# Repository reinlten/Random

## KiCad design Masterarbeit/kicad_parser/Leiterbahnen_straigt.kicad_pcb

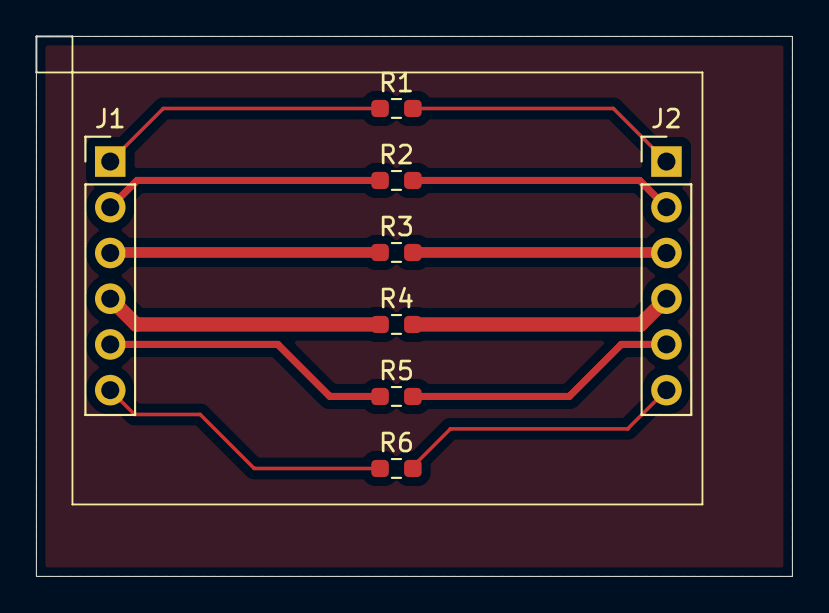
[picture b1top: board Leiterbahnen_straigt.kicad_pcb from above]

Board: 2 copper layers, 42.0 x 30.0 mm, 8 parts (0 on the bottom side), 12 nets.

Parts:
J1, J2: Conn_01x06_Pin; PinHeader_1x06_P2.54mm_Vertical
R1, R2, R3, R4, R5, R6: 50; R_0603_1608Metric_Pad0.98x0.95mm_HandSolder

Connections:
unnamed: J1.1, R1.1
unnamed: J1.2, R2.1
unnamed: J1.3, R3.1
unnamed: J1.4, R4.1
unnamed: J1.5, R5.1
unnamed: J1.6, R6.1
unnamed: J2.1, R1.2
unnamed: J2.2, R2.2
unnamed: J2.3, R3.2
unnamed: J2.4, R4.2
unnamed: J2.5, R5.2
unnamed: J2.6, R6.2

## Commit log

2024-06-29 zeuuuch
2024-06-30 active diode macht brrrrrrrt
2024-12-10 uni zeug
2024-12-10 FP update (PySpice)
2024-12-11 formatierung in matplotlib verbessert
2024-12-11 more data
2024-12-11 more graphs
2024-12-11 robotics I Bl 09
2024-12-15 init
2025-05-28 updated subckt
2025-06-05 struct change
2025-06-05 init: check results from optimisation
2025-06-05 full optimisation implemented
2025-06-05 cleanup
2025-06-14 measurement with testv3
2025-06-16 added filter
2025-07-17 replaced casc validation resistor with curr src
2025-07-17 tested new values
2025-07-18 results of casc sim
2025-07-18 new sim using switches instead of opv+mosfet
2025-07-18 new sim using switches instead of opv+mosfet running parallel
2025-07-18 casc sim parallelized
2025-07-18 switch sim parallelized
2025-07-24 calculated solutions
2025-07-24 init: calculates best effs from file
2025-07-24 init: whole simulation (with switches)
2025-07-24 changed some params
2025-08-06 renamed -- will not be used.
2025-08-06 changed sweep values
2025-08-06 removed diode CDBZ
2025-08-06 slight param changes
2025-08-28 curr calc enabled
